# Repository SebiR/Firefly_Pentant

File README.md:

# Firefly pendant
A green LED inside a small glass bottle looks like a caught firefly.
It is battery powered and can be used as decoration or jewelry.

## Features
* powered by a single CR2032
* Can drive two LEDs 
* Can be switched on and off with a button
* Uses deep sleep for long battery life

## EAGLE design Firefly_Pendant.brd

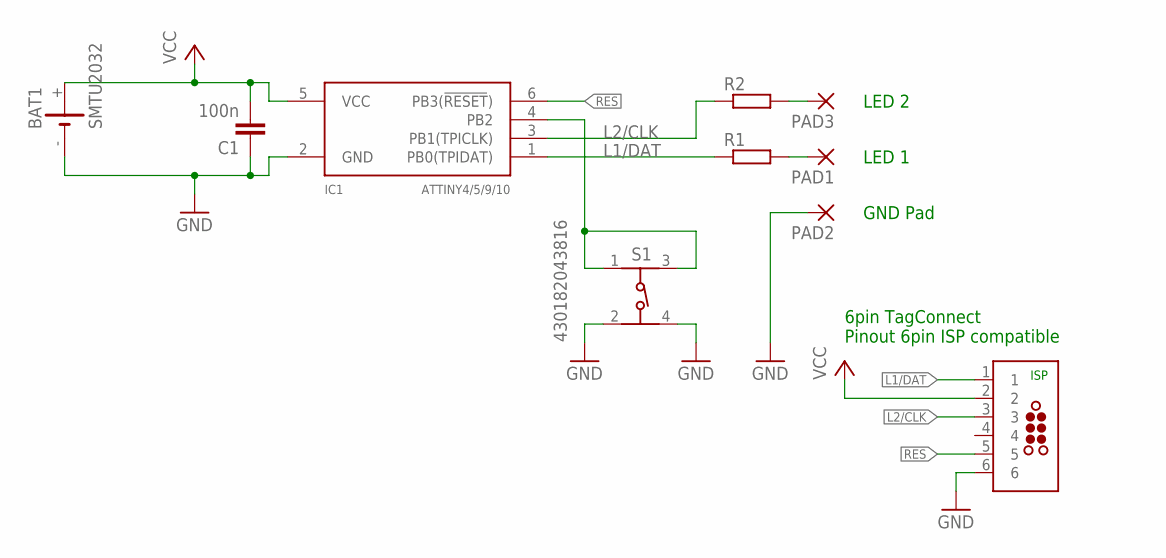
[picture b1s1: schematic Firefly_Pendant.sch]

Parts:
BAT1: SMTU2032
C1: 100n; C0603
IC1: ATTINY4/5/9/10; SOT23-6
J1: TAG-CONNECT_TC2030-MCP-NL
PAD1, PAD2, PAD3: WIREPADSMD1,27-254; SMD1,27-2,54
R1, R2: R-EU_R0603; R0603
S1: 430182043816

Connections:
GND: BAT1.-, C1.1, IC1.2 (GND), J1.6, PAD2.1, S1.2, S1.4
L1/DAT: IC1.1 (PB0(TPIDAT)), J1.1, R1.1
L2/CLK: IC1.3 (PB1(TPICLK)), J1.3, R2.1
unnamed: PAD1.1, R1.2
unnamed: IC1.4 (PB2), S1.1, S1.3
unnamed: PAD3.1, R2.2
RES: IC1.6 (PB3(!RESET!)), J1.5
VCC: BAT1.+, C1.2, IC1.5 (VCC), J1.2

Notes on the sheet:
ISP
6pin TagConnect Pinout 6pin ISP compatible
GND Pad
LED 1
LED 2

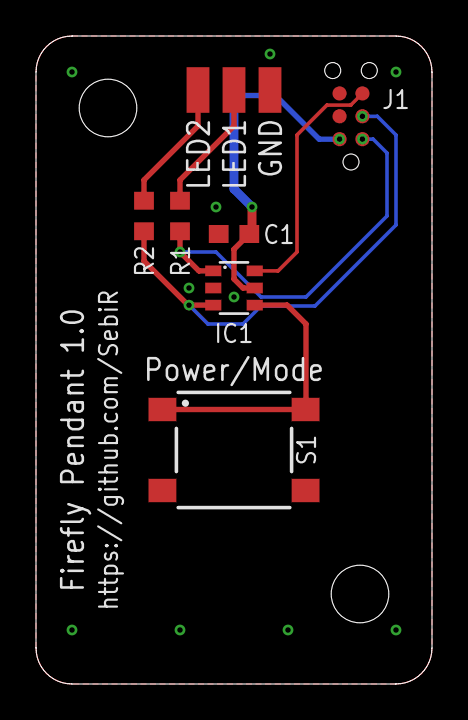
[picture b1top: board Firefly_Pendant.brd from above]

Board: 2 copper layers, 22.0 x 36.0 mm, 10 parts (1 on the bottom side), 8 nets.

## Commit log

2024-12-31 Scaled down clock a lot to save more power
2025-01-04 minor clean-ups
2025-01-06 Moved from internal RC oscillator to WDT oscillator to save even more current
2025-01-06 Used PRR (power reduction register) to shut down ADC and Timer0
2025-04-13 * Removed testing FW * Moved WDT configuration from own function into setup()

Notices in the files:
parts and their libraries:
Eigene-Rietig: ©2009 ROFA.cz - modified and updated by Robert Darlington ‹rdarlington@gmail.com›
Wurth_Switch_WS-TASV: Copyright: Würth Elektronik
